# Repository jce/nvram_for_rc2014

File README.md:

## NVRAM module for the RC2014.
Pages the lower 32K out when the ROM module is present. Does not forget its content even when powered off. Therefore can be used as program storage in addition to remanent data.

Data and address traces are mostly connected in sequence. This means the ordering is slightly jumbled. But writing and reading back memory content makes the same transformations so this is functionally fine.

Errata for building pcb V 1.1 (actual, and in picture):
- Typo in ic name: 74HTC32 should be 74HCT32
- Resistor and capacitor value not in drawing / on silkscreen
- Hole in RC2014 standard is missing
- "Page" pin is on SPARE1, instead of the second pinheader row, which is absent.

Errata for building of the V 1.0 proto:
- 74LS32 should be 74HTC32
- RC2014bus pin1 is not indicated
- IC types are not on silkscreen
- Pull up resistor value is missing: 10K
- Partlist missing
- Ground issues. Bridge some ground planes if you want to use this proto!
- Top memory is the bottom ic, ic's are reversed.

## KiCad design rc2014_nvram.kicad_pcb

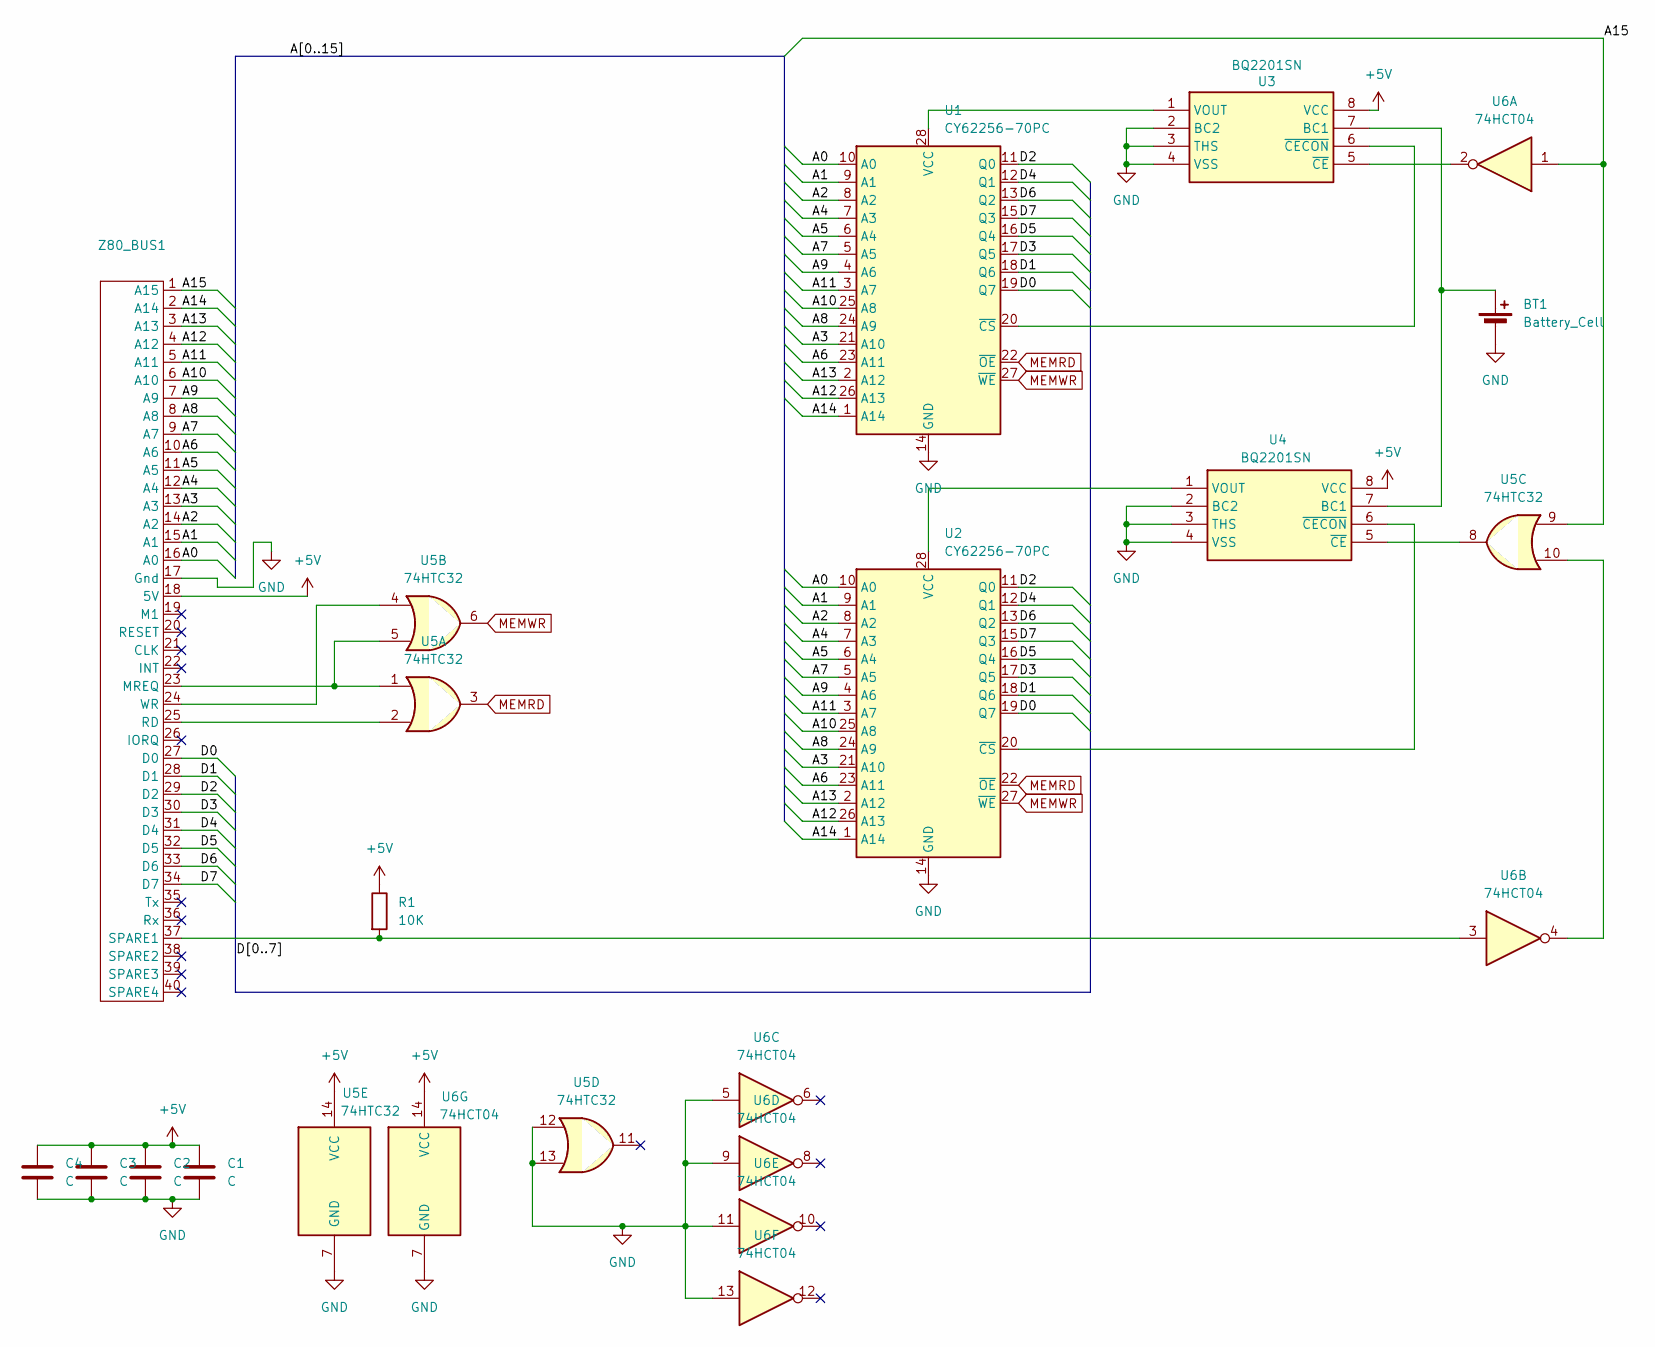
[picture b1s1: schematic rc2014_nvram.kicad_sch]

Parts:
BT1: Battery_Cell; ER14505
C1, C2, C3, C4: C; C_Rect_L4.6mm_W2.0mm_P2.50mm_MKS02_FKP02
R1: 10K; R_Axial_DIN0207_L6.3mm_D2.5mm_P10.16mm_Horizontal
U1, U2: CY62256-70PC; DIP-28_W15.24mm
U3, U4: BQ2201SN; SOIC127P600X175-8N; Mouser Part Number 595-BQ2201SN-N
U5: 74HTC32; DIP-14_W7.62mm_Socket_LongPads
U6: 74HCT04; DIP-14_W7.62mm_Socket_LongPads
Z80_BUS1: PinHeader_1x40_P2.54mm_Horizontal

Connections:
+5V: C1.1, C2.1, C3.1, C4.1, R1.1, U3.8 (VCC), U4.8 (VCC), U5.14 (VCC), U6.14 (VCC), Z80_BUS1.18 (5V)
/A0: U1.10 (A0), U2.10 (A0), Z80_BUS1.16 (A0)
/A1: U1.9 (A1), U2.9 (A1), Z80_BUS1.15 (A1)
/A2: U1.8 (A2), U2.8 (A2), Z80_BUS1.14 (A2)
/A3: U1.21 (A10), U2.21 (A10), Z80_BUS1.13 (A3)
/A4: U1.7 (A3), U2.7 (A3), Z80_BUS1.12 (A4)
/A5: U1.6 (A4), U2.6 (A4), Z80_BUS1.11 (A5)
/A6: U1.23 (A11), U2.23 (A11), Z80_BUS1.10 (A6)
/A7: U1.5 (A5), U2.5 (A5), Z80_BUS1.9 (A7)
/A8: U1.24 (A9), U2.24 (A9), Z80_BUS1.8 (A8)
/A9: U1.4 (A6), U2.4 (A6), Z80_BUS1.7 (A9)
/A10: U1.25 (A8), U2.25 (A8), Z80_BUS1.6 (A10)
/A11: U1.3 (A7), U2.3 (A7), Z80_BUS1.5 (A11)
/A12: U1.26 (A13), U2.26 (A13), Z80_BUS1.4 (A12)
/A13: U1.2 (A12), U2.2 (A12), Z80_BUS1.3 (A13)
/A14: U1.1 (A14), U2.1 (A14), Z80_BUS1.2 (A14)
/A15: U5.9, U6.1, Z80_BUS1.1 (A15)
/D0: U1.19 (Q7), U2.19 (Q7), Z80_BUS1.27 (D0)
/D1: U1.18 (Q6), U2.18 (Q6), Z80_BUS1.28 (D1)
/D2: U1.11 (Q0), U2.11 (Q0), Z80_BUS1.29 (D2)
/D3: U1.17 (Q5), U2.17 (Q5), Z80_BUS1.30 (D3)
/D4: U1.12 (Q1), U2.12 (Q1), Z80_BUS1.31 (D4)
/D5: U1.16 (Q4), U2.16 (Q4), Z80_BUS1.32 (D5)
/D6: U1.13 (Q2), U2.13 (Q2), Z80_BUS1.33 (D6)
/D7: U1.15 (Q3), U2.15 (Q3), Z80_BUS1.34 (D7)
GND: BT1.2 (-), C1.2, C2.2, C3.2, C4.2, U1.14 (GND), U2.14 (GND), U3.2 (BC2), U3.3 (THS), U3.4 (VSS), U4.2 (BC2), U4.3 (THS), U4.4 (VSS), U5.7 (GND), U5.12, U5.13, U6.5, U6.7 (GND), U6.9, U6.11, U6.13, Z80_BUS1.17 (Gnd)
MEMRD: U1.22 (~OE), U2.22 (~OE), U5.3
MEMWR: U1.27 (~WE), U2.27 (~WE), U5.6
unnamed: BT1.1 (+), U3.7 (BC1), U4.7 (BC1)
unnamed: U1.28 (VCC), U3.1 (VOUT)
unnamed: U1.20 (~CS), U3.6 (~CECON)
unnamed: U2.28 (VCC), U4.1 (VOUT)
unnamed: U2.20 (~CS), U4.6 (~CECON)
unnamed: U3.5 (~CE), U6.2
unnamed: U4.5 (~CE), U5.8
unnamed: U5.10, U6.4
unnamed: U5.1, U5.5, Z80_BUS1.23 (MREQ)
unnamed: U5.2, Z80_BUS1.25 (RD)
unnamed: R1.2, U6.3, Z80_BUS1.37 (SPARE1)
unnamed: U5.4, Z80_BUS1.24 (WR)

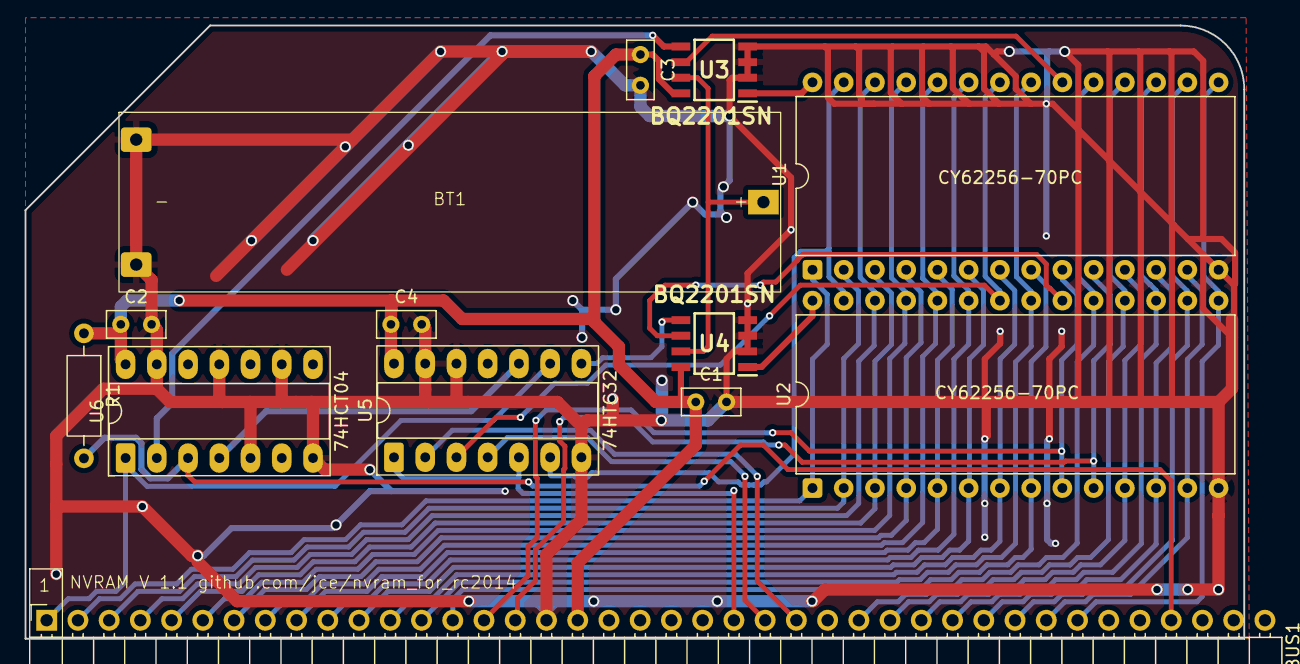
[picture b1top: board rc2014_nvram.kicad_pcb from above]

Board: 2 copper layers, 99.1 x 49.9 mm, 13 parts (0 on the bottom side), 40 nets.

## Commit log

2026-03-05 V 1.0, first proto run
2026-03-08 added schematic pdf
2026-03-08 Added readme, license
2026-03-08 Errata added
2026-03-13 Added more errata
2026-03-14 Fix grounding issues
2026-03-16 V 1.1, second proto run
2026-03-24 V 1.1 as build
2026-03-25 updated screenshot
